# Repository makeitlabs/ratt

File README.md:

Ongoing effort to expand and improve our RFID access control system beyond building doors and onto tools and equipment.

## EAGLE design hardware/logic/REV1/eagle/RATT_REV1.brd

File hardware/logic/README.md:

# RATT Logic Board

Design, fabrication files, and assembly documentation for the RATT logic board.

- `REV0` - Initial prototype (white PCB) - February 2018
- `REV1` - Design fixes (black PCB) - December 2018

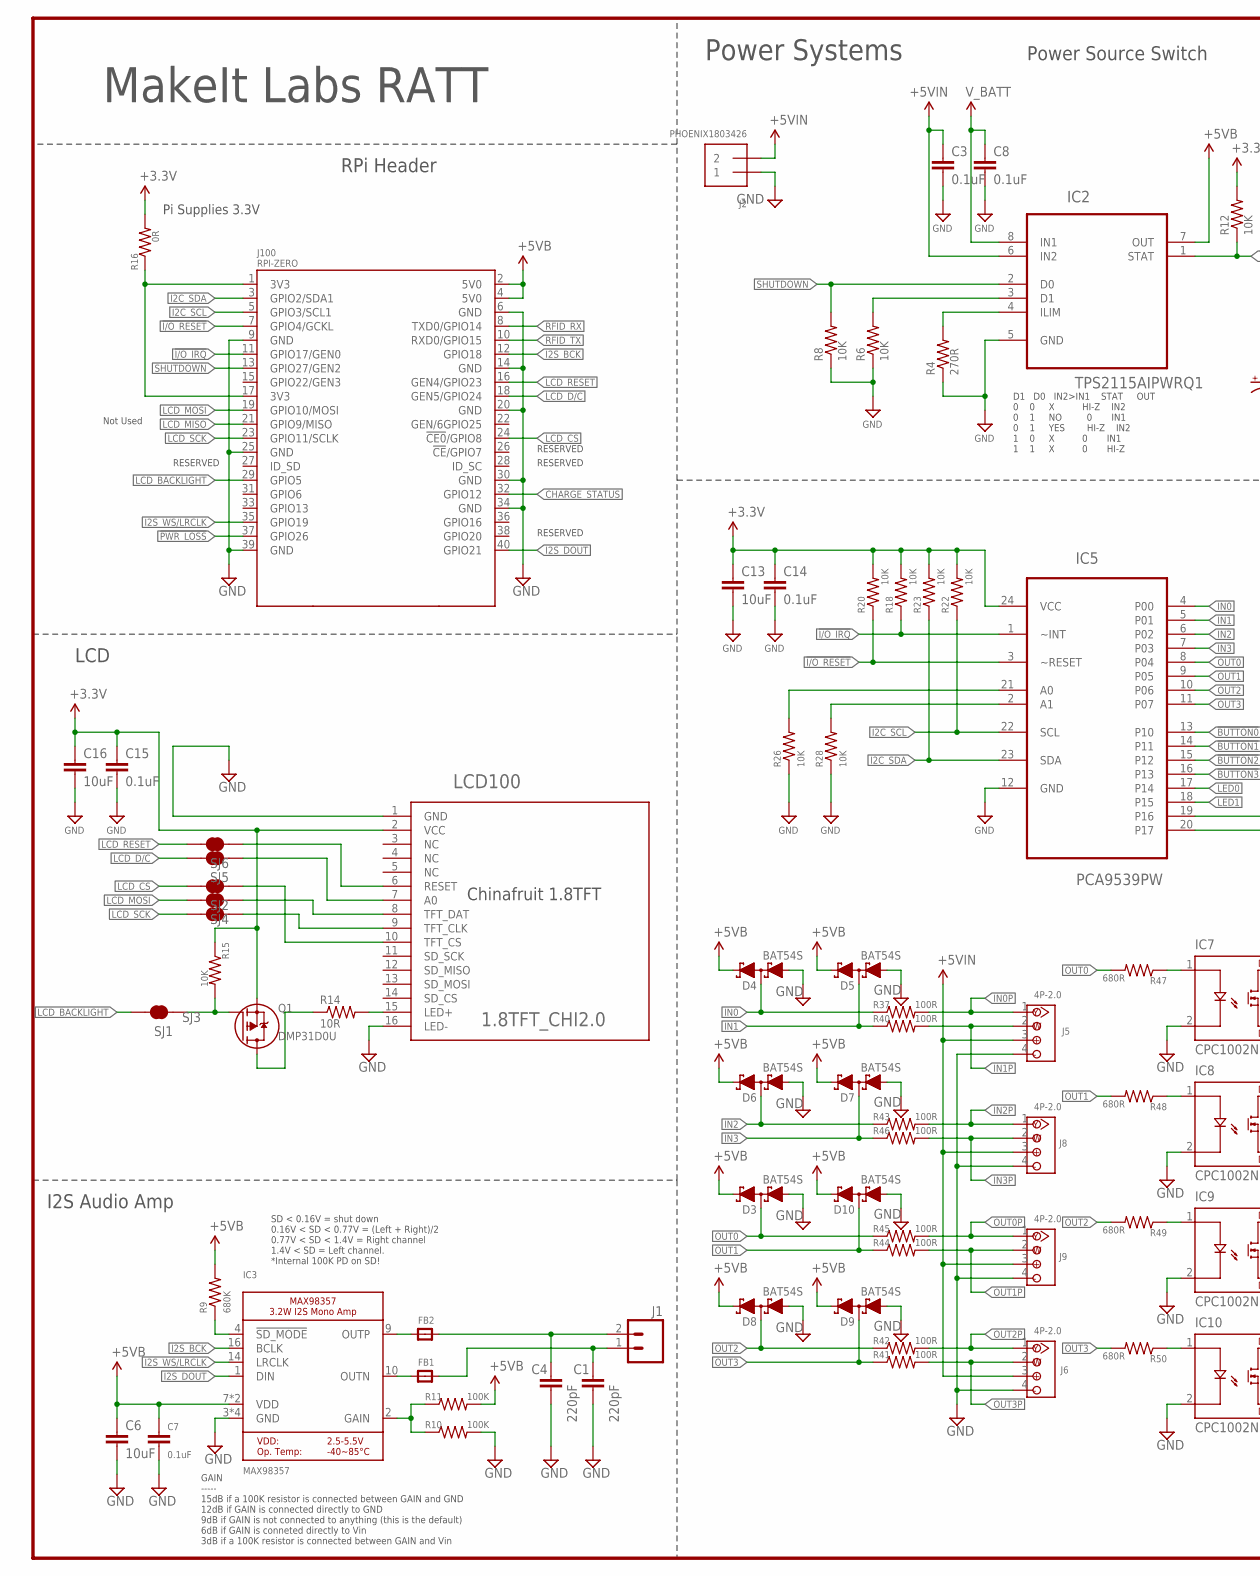
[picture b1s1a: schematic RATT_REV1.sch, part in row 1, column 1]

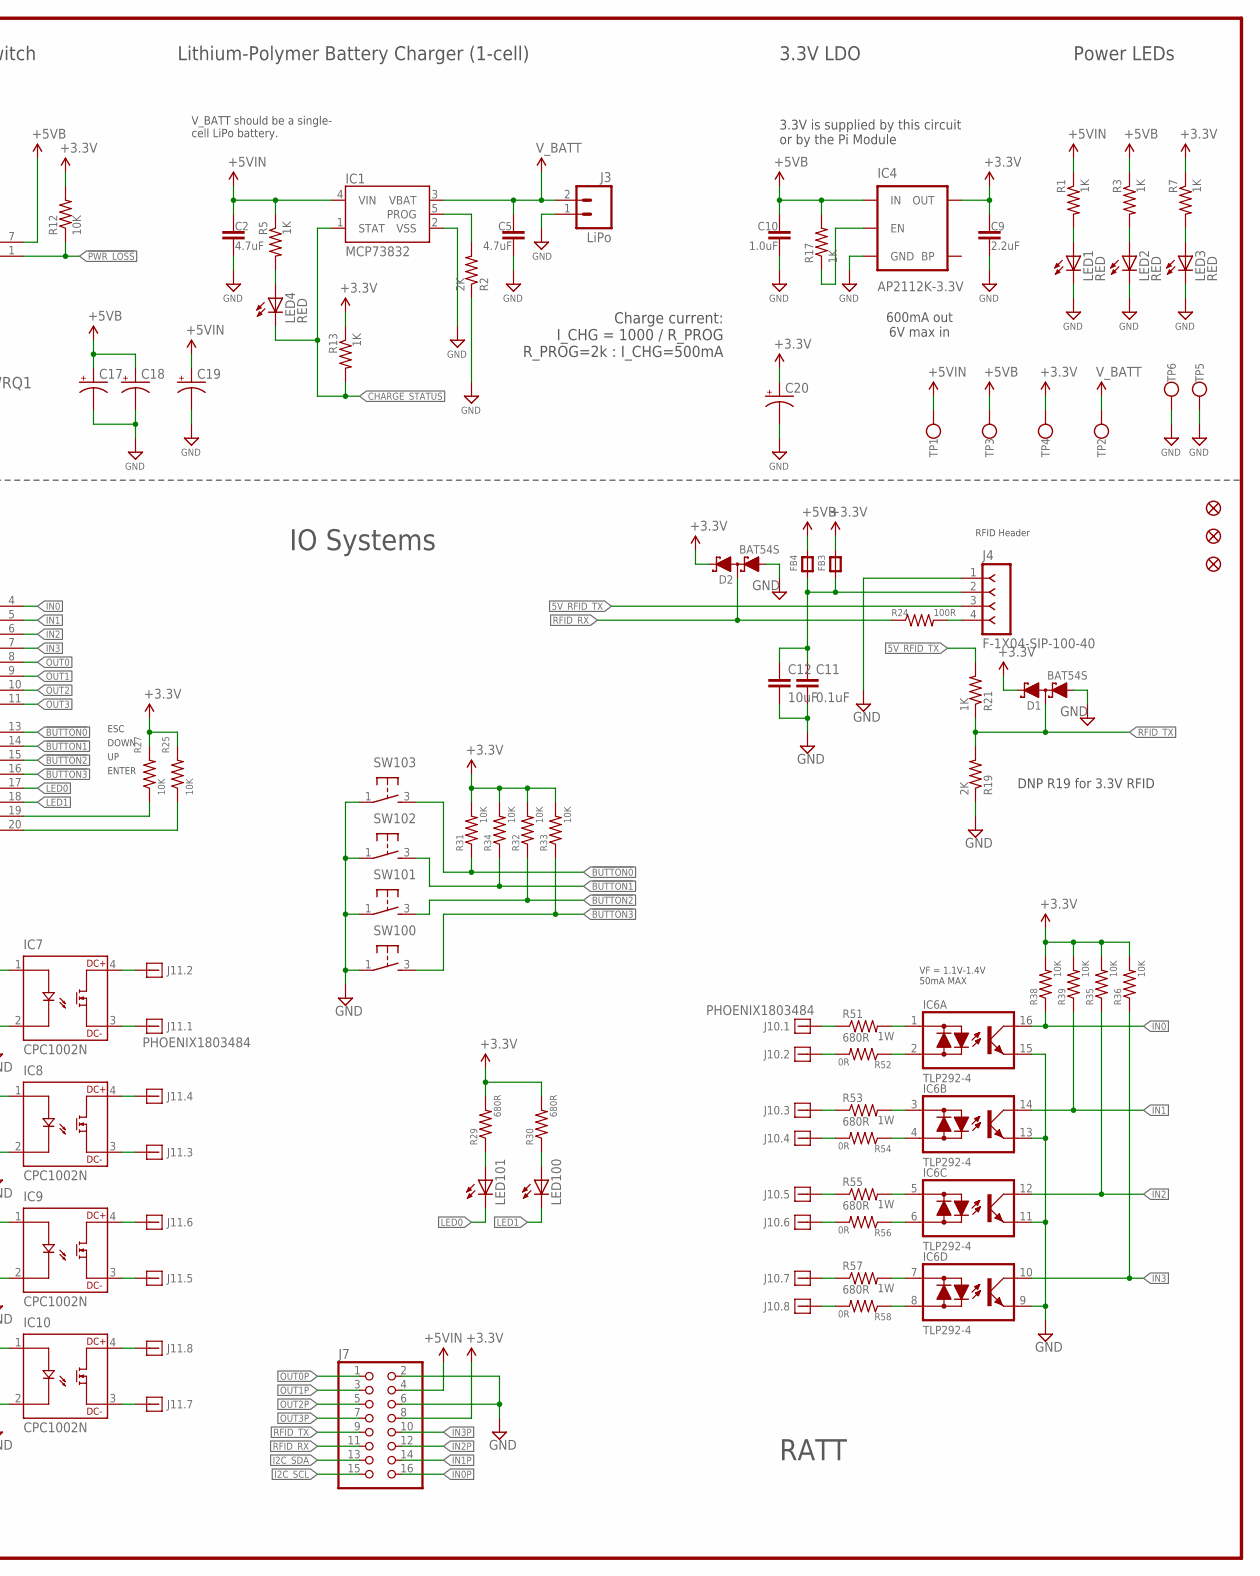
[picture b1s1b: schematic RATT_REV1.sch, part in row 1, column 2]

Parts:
C1, C4: 220pF; 0603-CAP
C2, C5: 4.7uF; 0603-CAP
C3, C8, C11, C14, C15: 0.1uF; 0603-CAP
C6, C12, C13, C16: 10uF; 0805-CAP
C7: 0.1uF; 0603-CAP; RATING X7R
C9: 2.2uF; 0603-CAP
C10: 1.0uF; 0603-CAP
C17, C18, C19, C20: CPOL-USD; PANASONIC_D
D1, D2, D3, D4, D5, D6, D7, D8, D9, D10: BAT54S; SOT-23
FB1, FB2, FB3, FB4: FERRITE; 0603
FID1, FID2, FID3: FIDUCIAL40MILX80MIL; FIDUCIAL-40MILX80MIL
IC1: MCP73832; SOT23-5
IC2: TPS2115AIPWRQ1; SOP65P640X120-8N
IC3: MAX98357; QFN16_3MM
IC4: AP2112K-3.3V; SOT23-5
IC5: PCA9539PW; SOP65P640X120-24N
IC6: TLP292-4; SO-16
IC7, IC8, IC9, IC10: CPC1002N
J1: M02POLAR; MOLEX-1X2
J2: PHOENIX1803426; 1803426
J3: LiPo; JST-2-PTH
J4: F-1X04-SIP-100-40; SIP-100-04-40
J5, J6, J8, J9: 4P-2.0; HW4-2.0
J7: PINHD-2X8SHROUD; 2X08_SHROUD
J10, J11: PHOENIX1803484; 1803484
J100: RPI-ZERO; RASPBERRYPI_BASTELSTUBE_V13_RASPI_BOARD_B+_FULL
LCD100: 1.8TFT_CHI2.0; 1.8TFT_CHI_2.0
LED1, LED2, LED3, LED4: RED; LED-0603
LED100, LED101: LED5MM
Q1: DMP31D0U; SOT23
R1, R3, R5, R7, R13, R17, R21: 1K; 0603-RES
R2, R19: 2K; 0603-RES
R4: 270R; 0603-RES
R6, R8, R12, R15, R18, R20, R22, R23, R25, R26, R27, R28, R31, R32, R33, R34, R35, R36, R38, R39: 10K; 0603-RES
R9: 680K; 0603-RES
R10, R11: 100K; 0603-RES
R14: 10R; 1206-RES
R16, R52, R54, R56, R58: 0R; 0603-RES
R24, R37, R40, R41, R42, R43, R44, R45, R46: 100R; 0603-RES
R29, R30, R47, R48, R49, R50: 680R; 0603-RES
R51, R53, R55, R57: 680R; 2512-RES
SJ1, SJ2, SJ3, SJ4, SJ5, SJ6: JUMPER-PAD-2-NC_BY_TRACE; SOLDERJUMPER_10MIL
SW100, SW101, SW102, SW103: ESWITCH_320; ESWITCH320
TP1: 5VIN; 1206-RCW
TP2: BATT; 1206-RCW
TP3: 5VB; 1206-RCW
TP4: 3.3V; 1206-RCW
TP5, TP6: GND; 1206-RCW

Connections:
3V3: J100.1 (3V3), J100.17 (3V3), R16.1
5V_RFID_TX: J4.3, R21.2
!BUTTON0: IC5.13 (P10), R31.1, SW103.3
!BUTTON1: IC5.14 (P11), R34.1, SW102.3
!BUTTON2: IC5.15 (P12), R32.1, SW101.3
!BUTTON3: IC5.16 (P13), R33.1, SW100.3
!I/O_IRQ: IC5.1 (~INT), J100.11 (GPIO17/GEN0), R18.1
!I/O_RESET: IC5.3 (~RESET), J100.7 (GPIO4/GCKL), R20.1
!PWR_LOSS: IC2.1 (STAT), J100.37 (GPIO26), R12.1
+3.3V: C9.1, C13.1, C14.1, C15.1, C16.1, C20.+, D1.2 (C2), D2.2 (C2), FB3.2, IC4.5 (OUT), IC5.24 (VCC), J7.8, LCD100.2 (VCC), Q1.2 (S), R7.1, R12.2, R13.1, R15.1, R16.2, R18.2, R20.2, R22.2, R23.2, R25.2, R27.2, R29.2, R30.2, R31.2, R32.2, R33.2, R34.2, R35.2, R36.2, R38.2, R39.2, TP4.1
+5VB: C6.1, C7.1, C10.1, C17.+, C18.+, D3.2 (C2), D4.2 (C2), D5.2 (C2), D6.2 (C2), D7.2 (C2), D8.2 (C2), D9.2 (C2), D10.2 (C2), FB4.2, IC2.7 (OUT), IC3.7 (VDD), IC3.8 (VDD), IC4.1 (IN), J100.2 (5V0), J100.4 (5V0), R3.1, R9.2, R11.2, R17.2, TP3.1
+5VIN: C2.1, C3.1, C19.+, IC1.4 (VIN), IC2.6 (IN2), J2.2, J5.3, J6.3, J7.4, J8.3, J9.3, R1.1, R5.1, TP1.1
CHARGE_STATUS: IC1.1 (STAT), J100.32 (GPIO12), LED4.C, R13.2
GND: C1.2, C2.2, C3.2, C4.2, C5.2, C6.2, C7.2, C8.2, C9.2, C10.2, C11.2, C12.2, C13.2, C14.2, C15.2, C16.2, C17.-, C18.-, C19.-, C20.-, D1.1 (A1), D2.1 (A1), D3.1 (A1), D4.1 (A1), D5.1 (A1), D6.1 (A1), D7.1 (A1), D8.1 (A1), D9.1 (A1), D10.1 (A1), IC1.2 (VSS), IC2.5 (GND), IC3.3 (GND), IC3.11 (GND), IC3.15 (GND), IC3.THERMAL (GND), IC4.2 (GND), IC5.12 (GND), IC6.9 (E), IC6.11 (E), IC6.13 (E), IC6.15 (E), IC7.2 (CATHODE), IC8.2 (CATHODE), IC9.2 (CATHODE), IC10.2 (CATHODE), J2.1, J3.1, J4.1, J5.4, J6.4, J7.2, J7.6, J8.4, J9.4, J100.6 (GND), J100.9 (GND), J100.14 (GND), J100.20 (GND), J100.25 (GND), J100.30 (GND), J100.34 (GND), J100.39 (GND), LCD100.1 (GND), LCD100.16 (LED-), LED1.C, LED2.C, LED3.C, R2.1, R4.1, R6.1, R8.1, R10.2, R19.1, R26.1, R28.1, SW100.1, SW101.1, SW102.1, SW103.1, TP5.1, TP6.1
I2C_SCL: IC5.22 (SCL), J7.15, J100.5 (GPIO3/SCL1), R22.1
I2C_SDA: IC5.23 (SDA), J7.13, J100.3 (GPIO2/SDA1), R23.1
I2S_BCK: IC3.16 (BCLK), J100.12 (GPIO18)
I2S_DOUT: IC3.1 (DIN), J100.40 (GPIO21)
I2S_WS/LRCLK: IC3.14 (LRCLK), J100.35 (GPIO19)
IN0: D4.3 (C1A2), IC5.4 (P00), IC6.16 (C), R37.1, R38.1
IN0P: J5.1, J7.16, R37.2
IN1: D5.3 (C1A2), IC5.5 (P01), IC6.14 (C), R39.1, R40.1
IN1P: J5.2, J7.14, R40.2
IN2: D6.3 (C1A2), IC5.6 (P02), IC6.12 (C), R35.1, R43.1
IN2P: J7.12, J8.1, R43.2
IN3: D7.3 (C1A2), IC5.7 (P03), IC6.10 (C), R36.1, R46.1
IN3P: J7.10, J8.2, R46.2
LCD_BACKLIGHT: J100.29 (GPIO5), SJ1.2
LCD_CS: J100.24 (!CE0!/GPIO8), SJ2.2
LCD_D/C: J100.18 (GEN5/GPIO24), SJ5.2
LCD_MISO: J100.21 (GPIO9/MISO)
LCD_MOSI: J100.19 (GPIO10/MOSI), SJ4.2
LCD_RESET: J100.16 (GEN4/GPIO23), SJ6.2
LCD_SCK: J100.23 (GPIO11/SCLK), SJ3.2
LED0: IC5.17 (P14), LED101.K (C)
LED1: IC5.18 (P15), LED100.K (C)
unnamed: IC3.2 (GAIN), R10.1, R11.1
unnamed: FB2.1, IC3.9 (OUTP)
unnamed: Q1.3 (D), R14.1
unnamed: FB1.1, IC3.10 (OUTN)
unnamed: IC3.4 (!SD_MODE), R9.1
unnamed: C1.1, FB1.2, J1.1
unnamed: C4.1, FB2.2, J1.2
unnamed: IC5.20 (P17), R25.1
unnamed: LCD100.15 (LED+), R14.2
unnamed: J4.4, R24.2
unnamed: LED3.A, R7.2
unnamed: LED2.A, R3.2
unnamed: IC5.19 (P16), R27.1
unnamed: IC1.5 (PROG), R2.2
unnamed: IC6.2 (AC2), R52.1
unnamed: LED4.A, R5.2
unnamed: IC4.3 (EN), R17.1
unnamed: IC6.1 (AC1), R51.2
unnamed: IC6.8 (AC2), R58.1
unnamed: IC5.21 (A0), R26.2
unnamed: IC5.2 (A1), R28.2
unnamed: IC6.7 (AC1), R57.2
unnamed: IC6.6 (AC2), R56.1
unnamed: IC6.5 (AC1), R55.2
unnamed: IC2.3 (D1), R6.2
unnamed: LCD100.6 (RESET), SJ6.1
unnamed: LCD100.7 (A0), SJ5.1
unnamed: LCD100.10 (TFT_CS), SJ2.1
unnamed: LCD100.8 (TFT_DAT), SJ4.1
unnamed: LCD100.9 (TFT_CLK), SJ3.1
unnamed: IC7.3 (DC-), J11.1
unnamed: Q1.1 (G), R15.2, SJ1.1
unnamed: IC6.4 (AC2), R54.1
unnamed: IC2.4 (ILIM), R4.2
unnamed: IC6.3 (AC1), R53.2
unnamed: J10.4, R54.2
unnamed: J10.3, R53.1
unnamed: J10.2, R52.2
unnamed: J10.1, R51.1
unnamed: J10.5, R55.1
unnamed: J10.6, R56.2
unnamed: J10.7, R57.1
unnamed: J10.8, R58.2
unnamed: LED101.A, R29.1
unnamed: LED100.A, R30.1
unnamed: LED1.A, R1.2
unnamed: C11.1, C12.1, FB3.1, FB4.1, J4.2
unnamed: IC7.1 (ANODE), R47.1
unnamed: IC7.4 (DC+), J11.2
unnamed: IC10.3 (DC-), J11.7
unnamed: IC8.1 (ANODE), R48.1
unnamed: IC10.4 (DC+), J11.8
unnamed: IC9.3 (DC-), J11.5
unnamed: IC9.4 (DC+), J11.6
unnamed: IC8.3 (DC-), J11.3
unnamed: IC8.4 (DC+), J11.4
unnamed: IC9.1 (ANODE), R49.1
unnamed: IC10.1 (ANODE), R50.1
OUT0: D3.3 (C1A2), IC5.8 (P04), R45.1, R47.2
OUT0P: J7.1, J9.1, R45.2
OUT1: D10.3 (C1A2), IC5.9 (P05), R44.1, R48.2
OUT1P: J7.3, J9.2, R44.2
OUT2: D8.3 (C1A2), IC5.10 (P06), R42.1, R49.2
OUT2P: J6.1, J7.5, R42.2
OUT3: D9.3 (C1A2), IC5.11 (P07), R41.1, R50.2
OUT3P: J6.2, J7.7, R41.2
RFID_RX: D2.3 (C1A2), J7.11, J100.8 (TXD0/GPIO14), R24.1
RFID_TX: D1.3 (C1A2), J7.9, J100.10 (RXD0/GPIO15), R19.2, R21.1
SHUTDOWN: IC2.2 (D0), J100.13 (GPIO27/GEN2), R8.2
V_BATT: C5.1, C8.1, IC1.3 (VBAT), IC2.8 (IN1), J3.2, TP2.1

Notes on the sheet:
GAIN ----- 15dB if a 100K resistor is connected between GAIN and GND 12dB if GAIN is connected directly to GND 9dB if GAIN is not connected to anything (this is the default) 6dB if GAIN is conneted directly to Vin 3dB if a 100K resistor is connected between GAIN and Vin
SD < 0.16V = shut down 0.16V < SD < 0.77V = (Left + Right)/2 0.77V < SD < 1.4V = Right channel 1.4V < SD = Left channel. *Internal 100K PD on SD!
V_BATT should be a single- cell LiPo battery.
Charge current: I_CHG = 1000 / R_PROG R_PROG=2k : I_CHG=500mA
Lithium-Polymer Battery Charger (1-cell)
600mA out 6V max in
RFID Header
RESERVED
ESC
DOWN
ENTER
VF = 1.1V-1.4V 50mA MAX
RPi Header
LCD
I2S Audio Amp
Pi Supplies 3.3V
3.3V is supplied by this circuit or by the Pi Module
D1 D0 IN2>IN1 STAT OUT 0 0 X HI-Z IN2 0 1 NO 0 IN1 0 1 YES HI-Z IN2 1 0 X 0 IN1 1 1 X 0 HI-Z
Power Systems
Power Source Switch
3.3V LDO
Power LEDs
IO Systems
RATT
MakeIt Labs RATT
Not Used
DNP R19 for 3.3V RFID

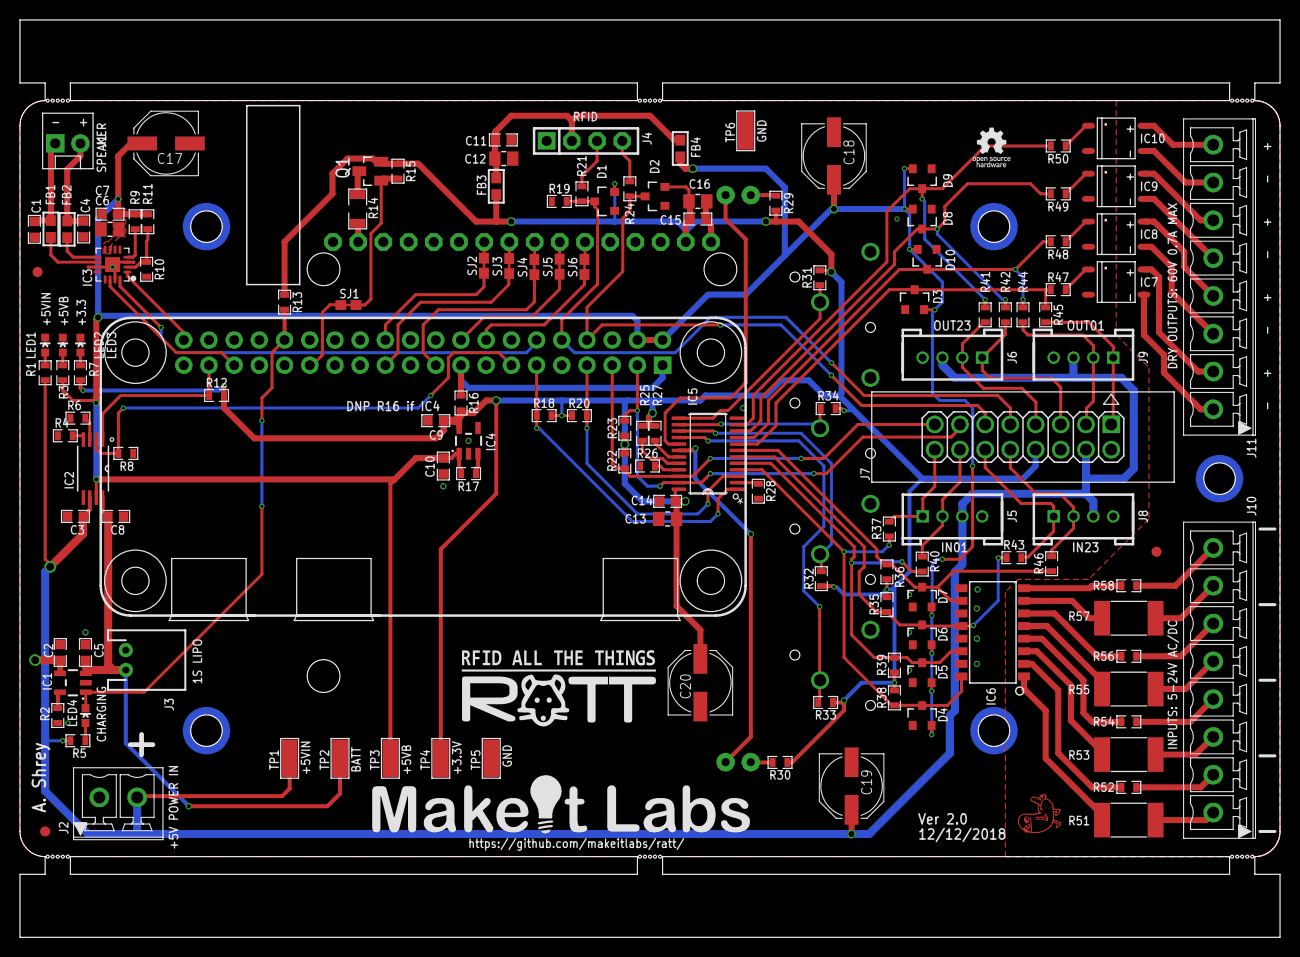
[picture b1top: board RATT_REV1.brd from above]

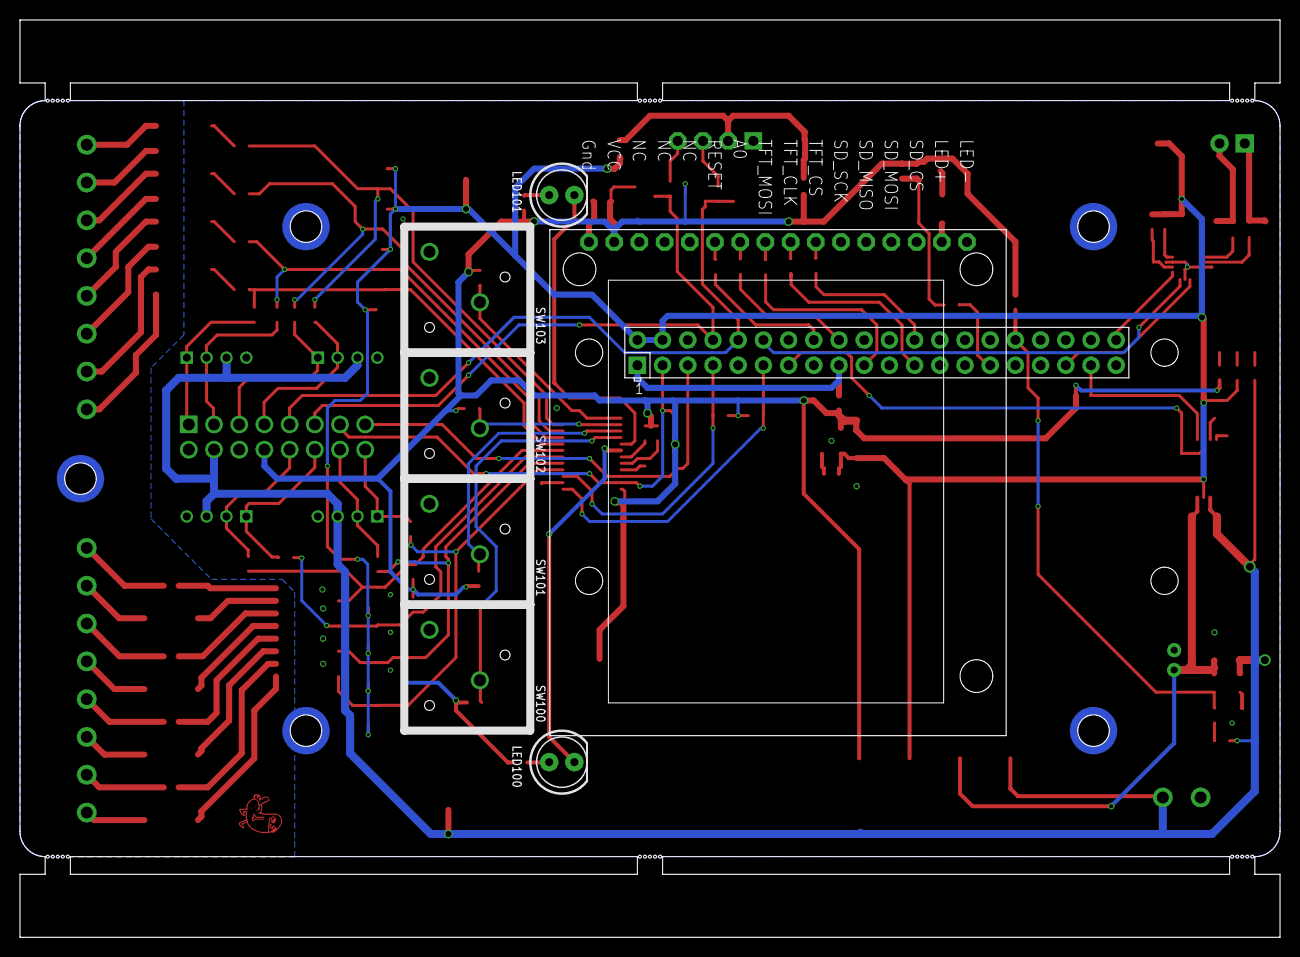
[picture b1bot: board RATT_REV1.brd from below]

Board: 2 copper layers, 127.0 x 92.5 mm, 141 parts (8 on the bottom side), 105 nets.

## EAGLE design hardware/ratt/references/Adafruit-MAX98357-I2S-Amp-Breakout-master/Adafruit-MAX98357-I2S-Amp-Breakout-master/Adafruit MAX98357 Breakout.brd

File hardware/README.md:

# RATT Hardware

- `ratt` - RATT hardware design (schematic, PCB)

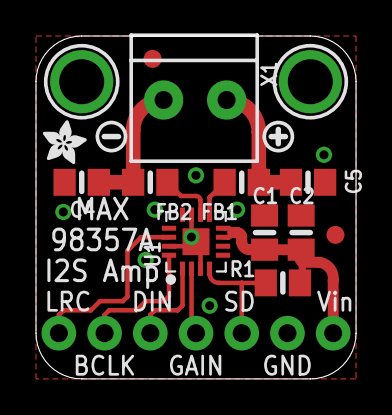
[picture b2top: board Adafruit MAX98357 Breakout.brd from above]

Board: 2 copper layers, 17.8 x 19.1 mm, 18 parts (1 on the bottom side), 11 nets.

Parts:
C1: 0.1uF; 0805-NO
C2: 10uF; 0805-NO
C4, C5: 220pF; 0805-NO
FB1, FB2: Ferrite; 0805-NO
FID1, FID2: FIDUCIAL""; FIDUCIAL_1MM
JP1: 1X07_ROUND_76
R1: 1M; 0805-NO
U1: MAX98357A; QFN16_3MM
U$6: SYMBOL_PLUS
U$9, U$10: MOUNTINGHOLE2.5; MOUNTINGHOLE_2.5_PLATED
U$11: SYMBOL_MINUS
U$14: ADAFRUIT_2.5MM
U$15: PCBFEAT-REV-040
X1: TERMBLOCK_1X2-3.5MM

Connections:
BCLK: JP1.6, U1.16
DIN: JP1.5, U1.1
GAIN: JP1.4, U1.2
GND: C1.2, C2.2, C4.2, C5.2, JP1.2, U1.3, U1.11, U1.15, U1.THERMAL
LRCLK: JP1.7, U1.14
unnamed: FB2.1, U1.10
unnamed: FB1.1, U1.9
SD_MODE: JP1.3, R1.1, U1.4
VDD: C1.1, C2.1, JP1.1, R1.2, U1.7, U1.8
VO+: C5.1, FB1.2, X1.2
VO-: C4.1, FB2.2, X1.1

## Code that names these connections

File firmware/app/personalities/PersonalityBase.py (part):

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    GPIO_PIN_LED1 = 508
    GPIO_PIN_LED2 = 509

    pinToName = {GPIO_PIN_SHUTDOWN : 'SHUTDOWN',
                 GPIO_PIN_POWER_PRESENT : 'POWER_PRESENT',
                 GPIO_PIN_CHARGE_STATE : 'CHARGE_STATE',
                 GPIO_PIN_LED1 : 'LED1',
                 GPIO_PIN_LED2 : 'LED2',
                 GPIO_PIN_IN0 : 'IN0',
                 GPIO_PIN_IN1 : 'IN1',
                 GPIO_PIN_IN2 : 'IN2',
                 GPIO_PIN_IN3 : 'IN3',
                 GPIO_PIN_OUT0 : 'OUT0',
                 GPIO_PIN_OUT1 : 'OUT1',
                 GPIO_PIN_OUT2 : 'OUT2',
                 GPIO_PIN_OUT3 : 'OUT3'}

    nameToPin = {'SHUTDOWN' : GPIO_PIN_SHUTDOWN,
                 'POWER_PRESENT' : GPIO_PIN_POWER_PRESENT,
                 'CHARGE_STATE' : GPIO_PIN_CHARGE_STATE,
                 'LED1' : GPIO_PIN_LED1,
                 'LED2' : GPIO_PIN_LED2,
                 'IN0' : GPIO_PIN_IN0,
                 'IN1' : GPIO_PIN_IN1,
                 'IN2' : GPIO_PIN_IN2,
                 'IN3' : GPIO_PIN_IN3,
                 'OUT0' : GPIO_PIN_OUT0,
                 'OUT1' : GPIO_PIN_OUT1,
                 'OUT2' : GPIO_PIN_OUT2,
                 'OUT3' : GPIO_PIN_OUT3}

    validScan = pyqtSignal(MemberRecord, name='validScan', arguments=['record'])
    invalidScan = pyqtSignal(str, name='invalidScan', arguments=['reason'])
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            self.pins_out[2].pinChanged.connect(self.slotSimGPIOPinChanged)
            self.pins_out[3].pinChanged.connect(self.slotSimGPIOPinChanged)

            self.pin_led1.pinChanged.connect(self.slotSimGPIOPinChanged)
            self.pin_led2.pinChanged.connect(self.slotSimGPIOPinChanged)
            self.pin_shutdown.pinChanged.connect(self.slotSimGPIOPinChanged)

    @pyqtSlot()
    def slotForceSimGPIOUpdate(self):
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            self.simGPIOPinChanged.emit(self.pinToName[self.pins_out[2].number], self.pins_out[2].value)
            self.simGPIOPinChanged.emit(self.pinToName[self.pins_out[3].number], self.pins_out[3].value)

            self.simGPIOPinChanged.emit(self.pinToName[self.pin_led1.number], self.pin_led1.value)
            self.simGPIOPinChanged.emit(self.pinToName[self.pin_led2.number], self.pin_led2.value)
            self.simGPIOPinChanged.emit(self.pinToName[self.pin_shutdown.number], self.pin_shutdown.value)


    # this slot handles pin changes for simulated GPIO and regenerates
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        self.pins_out.append(self.gpio.alloc_pin(self.GPIO_PIN_OUT2, GPIO.OUTPUT))
        self.pins_out.append(self.gpio.alloc_pin(self.GPIO_PIN_OUT3, GPIO.OUTPUT))

        self.pin_led1 = self.gpio.alloc_pin(self.GPIO_PIN_LED1, GPIO.OUTPUT, active_low=1)
        self.pin_led2 = self.gpio.alloc_pin(self.GPIO_PIN_LED2, GPIO.OUTPUT, active_low=1)

        self.pin_shutdown = self.gpio.alloc_pin(self.GPIO_PIN_SHUTDOWN, GPIO.OUTPUT)
        self.pin_shutdown.set(GPIO.HIGH)

        self.pin_powerpresent = self.gpio.alloc_pin(self.GPIO_PIN_POWER_PRESENT, GPIO.INPUT, self.__power_event, GPIO.BOTH)
        self.pin_charge_state = self.gpio.alloc_pin(self.GPIO_PIN_CHARGE_STATE, GPIO.INPUT)

        self.nameToPinObject = {'SHUTDOWN' : self.pin_shutdown,
                                'POWER_PRESENT' : self.pin_powerpresent,
                                'CHARGE_STATE' : self.pin_charge_state,
                                'LED1' : self.pin_led1,
                                'LED2' : self.pin_led2,
                                'IN0' : self.pins_in[0],
                                'IN1' : self.pins_in[1],
                                'IN2' : self.pins_in[2],
                                'IN3' : self.pins_in[3],
                                'OUT0' : self.pins_out[0],
                                'OUT1' : self.pins_out[1],
                                'OUT2' : self.pins_out[2],
                                'OUT3' : self.pins_out[3]}


    # de-allocate the gpio pins, EXCEPT for the shutdown pin (because that would potentially turn RATT off)
    def __deinit_gpio_pins(self):
        for pin in self.gpio.available_pins:
            if pin != self.GPIO_PIN_SHUTDOWN:
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
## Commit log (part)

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2018-03-11 tool safety check->tool enabled->tool active/inactive roughed and working
2018-03-13 bump meta-ratt
2018-03-13 add in front panel LED support
2018-03-18 fix for unexplained occasional EOF on read of GPIO value
2018-11-13 meta-ratt change to sumo-mender branch
2018-11-13 add meta-mender as git submodule
2018-11-13 housekeeping, moved an old test into the attic, updated main firmware README
2018-11-14 changes to use miniuart for RFID (ttyS0).. would like to get back to using PL011 (ttyAMA0) when disabling bt on pi-0w w/uboot works
2018-11-21 early skeleton of mqtt client implementation
2018-11-21 add samba and cifs-utils to build for rapid development
2018-11-24 implements targeted mqtt messages in addition to broadcast messages - ratt/node/[mac addr in lowercase no colons]/subtopic
2018-11-25 add some padding
2018-11-25 fixes to lockout message scroller
2018-11-26 change acl update mqtt structure (see spec)
2018-11-26 restructure personality lock/unlock mqtt messages (see spec)
2018-11-26 add base url to .ini file to more easily swap between development and real backend
2018-11-29 moving cert generating junk from the old ESP32 days since it'll be a useful starting point
2018-11-29 repoint SSL cert/keyfiles to /data/certs on persistent partition
2018-11-29 git ignore for ssl directory (generated certs/keys that should not be committed)
2018-12-02 add wiring diagram for full spectrum integration
2018-12-02 move the mqtt stuff into a thread to avoid blocking behavior on connections. also adds broker connect/disconnect signal and personality base will now broadcast state on mqtt when reconnecting
2018-12-02 a few aesthetic tweaks to views
2018-12-03 rework a bunch of mqtt message structures and adds some functionality too (see spec)
2018-12-03 add pdf of schematic to hw dir
2018-12-04 play audio on successful rfid scan when reporting an issue
2018-12-04 fix permissions
2018-12-04 renamed
2018-12-04 if iwconfig returns 'No such device' make some simulated wifi status for simulator
2018-12-04 adds simulated gpio, not really functional yet but it allows app to run on devhost.
2018-12-04 remove unused pro file
2018-12-04 adds simulated RFID valid & invalid scan from diags for dev host testing
2018-12-04 start of README for app doc, mostly describes how to run dev host version for now
2018-12-04 fix derp, add simulated tag value from config file for faster devel/debug cycles
2018-12-05 basic functionality on simulated input pins, rework the sim i/o signal/slots to use names instead of numbers
2018-12-05 temporary workaround since argparser does not seem to be on embedded target
2018-12-05 adding new icons
2018-12-06 remove argparser hack (added argparser + other python libs to image)
2018-12-06 fixed fonts on the ratt image, so now set a global font for the app
2018-12-07 fix holes
2018-12-08 rework how the paho event loop is called in the mqtt thread
2018-12-08 adds new config opts
2018-12-08 default mqtt publishes to qos=2, allow override. also provide retain option
2018-12-08 add TOOL_ENABLED_NOT_POWERED state to better handle exiting active state when tool power lost, generates mqtt logout msg with 'toolpower' reason, play logout sound effect
2018-12-11 move MQTT SSL enable to new option MQTT.SSL
2018-12-11 move RFID sound effect triggers from here into ViewAccess
2018-12-11 add "not powered denied" state to provide feedback when scanning RFID when the tool is not powered up
2018-12-11 import fabfile for doing development-level app updates on remote target - rough and probably dangerous!
2018-12-11 fix bug where unlocked state was not reported on mqtt if locked out (it was only reporting when pending)
2018-12-14 REV1 as sent out to fab
2018-12-14 hardware files housekeeping phase 2
2018-12-14 yet another reorg, structured with revision at the root and broken out to eagle, fab and assembly within each rev
2018-12-21 adding REV1 (aka version 2) assembly drawings/PDF schematic/DXF outline
2018-12-29 created parts sheet for hand assembly of boards
2018-12-31 fix clobbered code
2019-01-04 wrap backlight code in try/except for devhost
2019-01-10 add audio instructions, key beeps and timeout for password, new issue report audio
2019-01-11 add lift integration wiring documentation
2019-01-18 add enclosure footprint dxf, pdf drawing, and datasheets from Polycase
2019-01-19 for homing: add speech audio prompts, improved nagging, a bunch of other tweaks
2019-01-19 add 60 sec timeout timer to wait for homing
2019-01-19 add optional external homing override for possible integration with rotary tool (on input 4). also makes manual override optionally available.
2019-01-31 adding B.O.I. (Big Obnoxious Indicator) mech files
2019-02-02 change logic on laser homing override
2019-02-02 fix regression with password mode
2019-02-02 use 'done()' in timeout exit
2019-02-02 add Arduino project for RGB LED indicator
2019-02-04 Adds new feature, if Personality.AllowForcedLogout=True, long-press on ESC during tool active will force a logout with mqtt reason=forced (stopgap for flaky lift sensor)
2019-02-09 work in progress for remote config support, not done
2019-02-09 housekeeping to refactor ACL.py to use CachedRemoteFile.py
2019-02-09 work in progress, still brain damaged
2019-02-11 emit personality/init message
2019-02-16 fix lurking bug with error handling in http downloader when incorrect credentials supplied for auth
2019-02-23 Fix a few startup issues when remote config can't be downloaded
2019-03-18 more doorbot schematic & pcb work
2019-03-21 more doorbot schematic & pcb, routed and passes drc but not complete
2019-03-21 add wiegand led/buzzer control, leds, some rerouting
2019-03-22 doorbot pcb rev0 draft 2 ready for review
2019-03-23 move duty cycle pot, try to fix mickey mouse corners on cutout
2019-03-23 fabrication files
2019-03-23 update placeholder resistors with calculated values
2019-03-24 add doorbot datasheets
2019-03-26 add current sense firmware for ATTiny85 (Arduino env)
2019-03-26 a few schematic value tweaks and adds bom for current sensor board
2019-03-29 adds admin timeout option (teaching/maint/etc.) - admins can long-press blue key when logged in to get longer timeout - addreses #5
2019-03-31 add assembly drawings for doorbot
2019-04-03 start of softserial-based calibration routine for current sensor
2019-04-28 somehow lost the laser cutter personality changes which actually enabled the tool...
2020-02-04 - ARM/ARMs can log-into locked-out resources - "Lockout" messages displays "message" (not JSON payload) - Admin timeout value works (used normal timeout before) - Laser ARMs/RMs can use blue button t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
2020-02-06 updating documentation for how to generate and deploy authbackend and Node-RED certs
2020-10-05 fix SSL error handler function signature
2020-10-06 remove a couple of brad's debug prints
2020-10-06 fix some openssl command errors in the cert scripts. not sure what changed but passing a config file option in is not valid for some of these commands.
2020-11-26 work in progress to port the circa Jan.2017 ESP32 RATT code to modern 2020 ESP-IDF
2020-11-27 rename ratt config options
2020-12-04 add beeper task, temporary hacks in rfid to actuate motor driver (will move to own task)
2020-12-06 fixes and cleanups in https
2020-12-06 rework network task, add mqtt client with client cert verification, still work in progress for testing
2020-12-06 split networking implementation out into task / https / mqtt
2020-12-06 add support for mqtt personality 'access' messages to log usage
2020-12-12 fix comment
2020-12-14 more schematic work.. power supply, lip charger, etc
    more schematic work.. power supply, lip charger, etc
2020-12-18 import actual board outline DXF and adjust rough placement
2020-12-22 fully routed, DRC'd, outlined w/breakaways, pending final review
2020-12-22 add rev0 fabrication files - pcb sent off to fab
2020-12-24 move uratt hw design into REV0 directory, add kicad backup files to git ignore list
2020-12-24 move RATT eagle library and Adam's random references directory into the RATT subproject
2020-12-24 add prelim doorbot alphanumeric I2C LCD project (stalled work in progress)
2020-12-27 add tig interface schematic
2020-12-27 rename uratt project
2021-01-01 work in progress porting to REV0 board
2021-01-02 add new gpio mapping header, use it in various files
2021-01-09 major rework adding main task, basic functionality - much more to do
2021-01-10 Add handwired TIG interface schematic PDF
2021-01-11 work in progress on REV1 schematic/PCB
2021-01-12 uratt REV1 work, remove front panel, place new parts, partial routing
2021-01-12 Add RATT REV1 BOM (bare CSV file straight from Eagle, grouped by REFDES)
2021-01-13 passes drc
2021-01-16 separate front panel board layout
2021-01-16 uratt REV1 change inductor, cleanups, add 3.3V motor option, silk work, 12 pin FFC
2021-01-16 generate fab files for uratt and uratt_fp
2021-11-04 Set theme jekyll-theme-slate
2021-11-24 uratt now moved to its own repo
2021-11-24 move doorbot hardware projects to doorbot repo
2021-11-24 remove meta-mender
2021-11-27 updates to app for python3 compatibility
2021-11-27 move poky setup to dunfell, make script more generic
2021-11-27 i/o reset changes, add process timing to sdimg copy
2021-11-28 add pre/post scripts to put text on console that raspi2fb will see while app starts/stops
2021-11-30 add build-env script to set up yocto build env
2021-12-01 remove defunct Telemetry class, clean up and comment ini files, create categories in config if they don't exist
2021-12-01 defer setting model of issues list until view is shown to avoid error/empty list
2021-12-01 change transitions on StackView
2021-12-01 move to regular json import instead of simplejson
2021-12-01 indicate tag counts are unique in GUI
2021-12-02 ignore buildhistory
2021-12-02 update build documentation for Dunfell, Ubuntu 20.04 etc.
2021-12-02 add create mountpoints option to sdimg_util
2021-12-02 build doc fixes
2021-12-03 updated meta-ratt
2021-12-04 app improvements: ACL update status in top bar, don't show stats if same hash, mender artifact info in version display, improved diags display
2021-12-04 lock root account (no password) - MUST template in an SSH key to log into unit. use date/time stamp as auto-versioning in MENDER_ARTIFACT_NAME
2021-12-04 improved .gitignore for templates since more template files now can exist
2021-12-04 add hosts example to templates
2021-12-04 ignore .ini files in ratt app to avoid accidentally committing passwords
2021-12-04 fix templating for SSH keys and permissions, update doc
2021-12-05 change mender artifact name format
2021-12-05 clean up old configs dir a bit, update README
2021-12-05 removing meta-jumpnow and meta-mender submodules; now cloned into poky-dunfell dependency tree
2021-12-05 update local.conf to point cache, tmp, oesources to ~/yocto-ratt instead of /u/rpi
2021-12-05 fix mqtt bug from py3 conversion, add long awaited mqtt message upon ACL update
2021-12-06 adjust script for new templates dir
2021-12-06 moved templates (i thought i already did this?)
2021-12-06 add a few sensible hosts entries to example template
2021-12-06 drop sim gpio default loglevel
2021-12-07 change level of log
2021-12-07 move current sense stuff
2021-12-07 move integration dir
2021-12-07 move yocto-build dir to yocto
2021-12-07 remove ratt app from main ratt repo and move to its own, primarily for versioning/release reasons
2021-12-08 rename sdimg_util.sh->imgfeast, vastly improve build-env.sh, create baker script that uses BB post config to reliably update mender artifact name every build, update docs
2022-08-21 Documentation for Epilog wiring
2022-12-23 update README for cert generaiton
2023-02-01 move docs to directories
2023-02-01 move Everlast TIG stuff to integrations directory
2026-04-05 MOPA UV Integration
2026-04-13 xTool UV Laser Integration

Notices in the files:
firmware/app/personalities/PersonalityBase.py:
Copyright 2018 MakeIt Labs
parts and their libraries:
microbuilder: This work is placed in the public domain, and may be freely used for commercial and non-commercial work with the following conditions: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
